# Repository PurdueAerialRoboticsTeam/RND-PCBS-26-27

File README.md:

2026-27 Git Repo for RND PCB designs. 25-26 reference designs available in archive

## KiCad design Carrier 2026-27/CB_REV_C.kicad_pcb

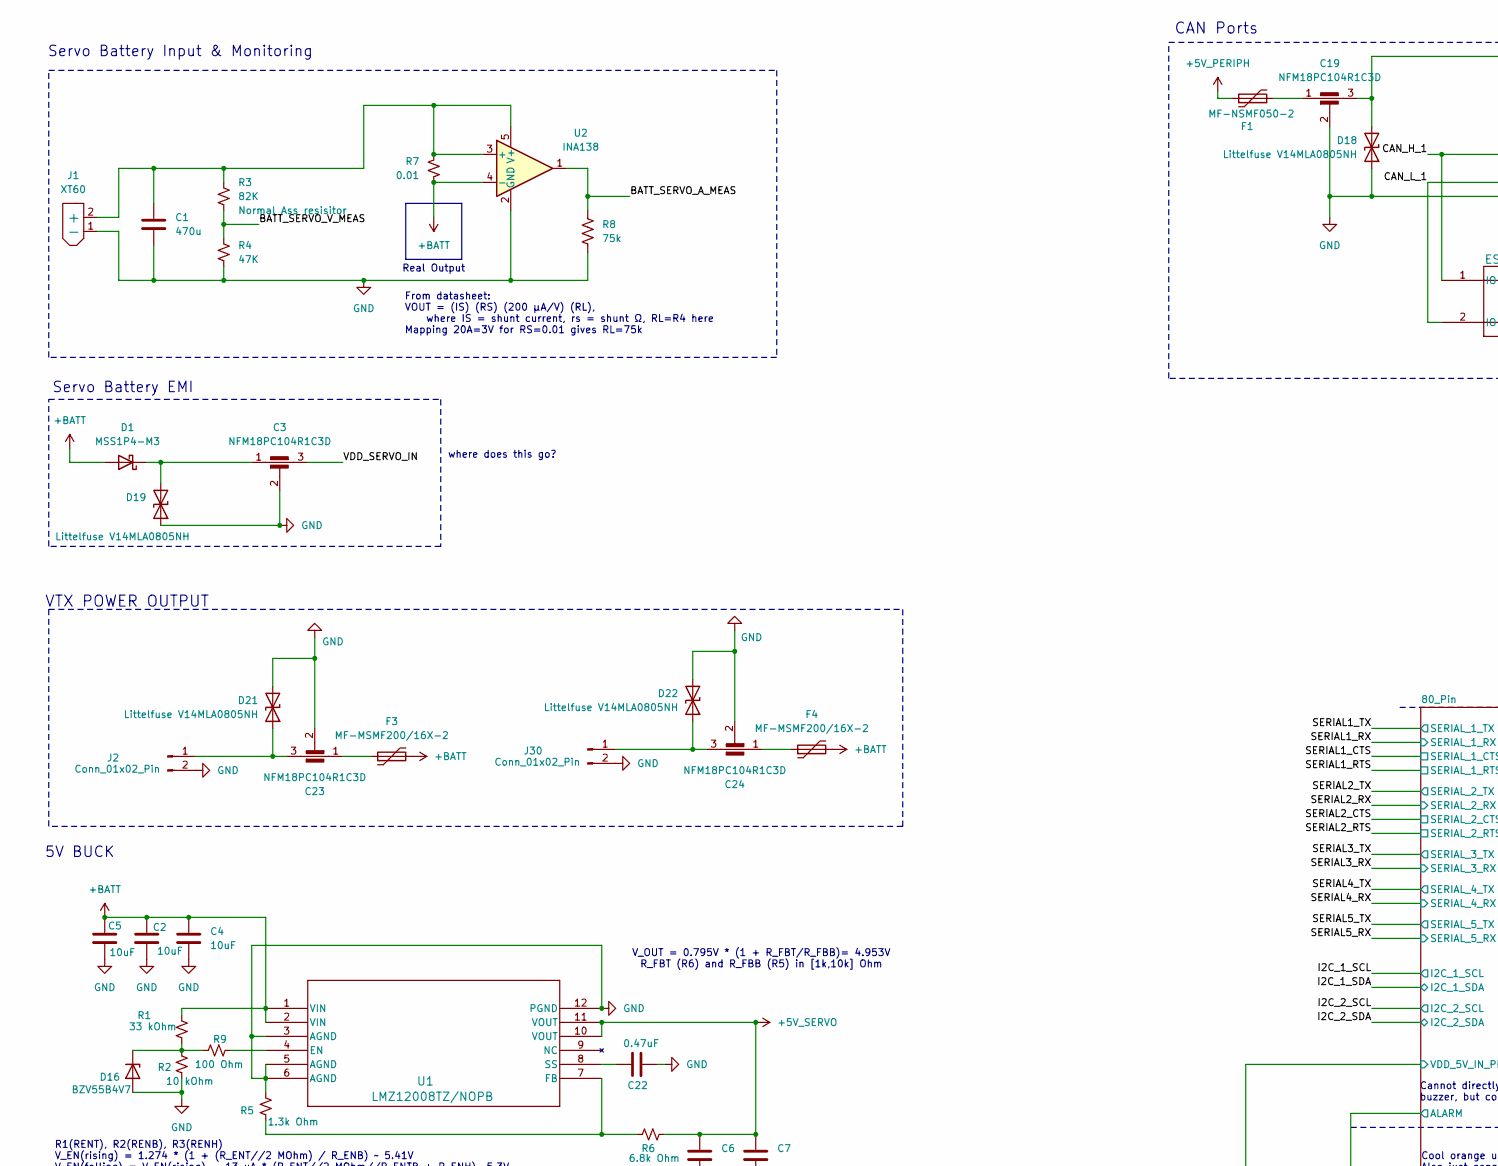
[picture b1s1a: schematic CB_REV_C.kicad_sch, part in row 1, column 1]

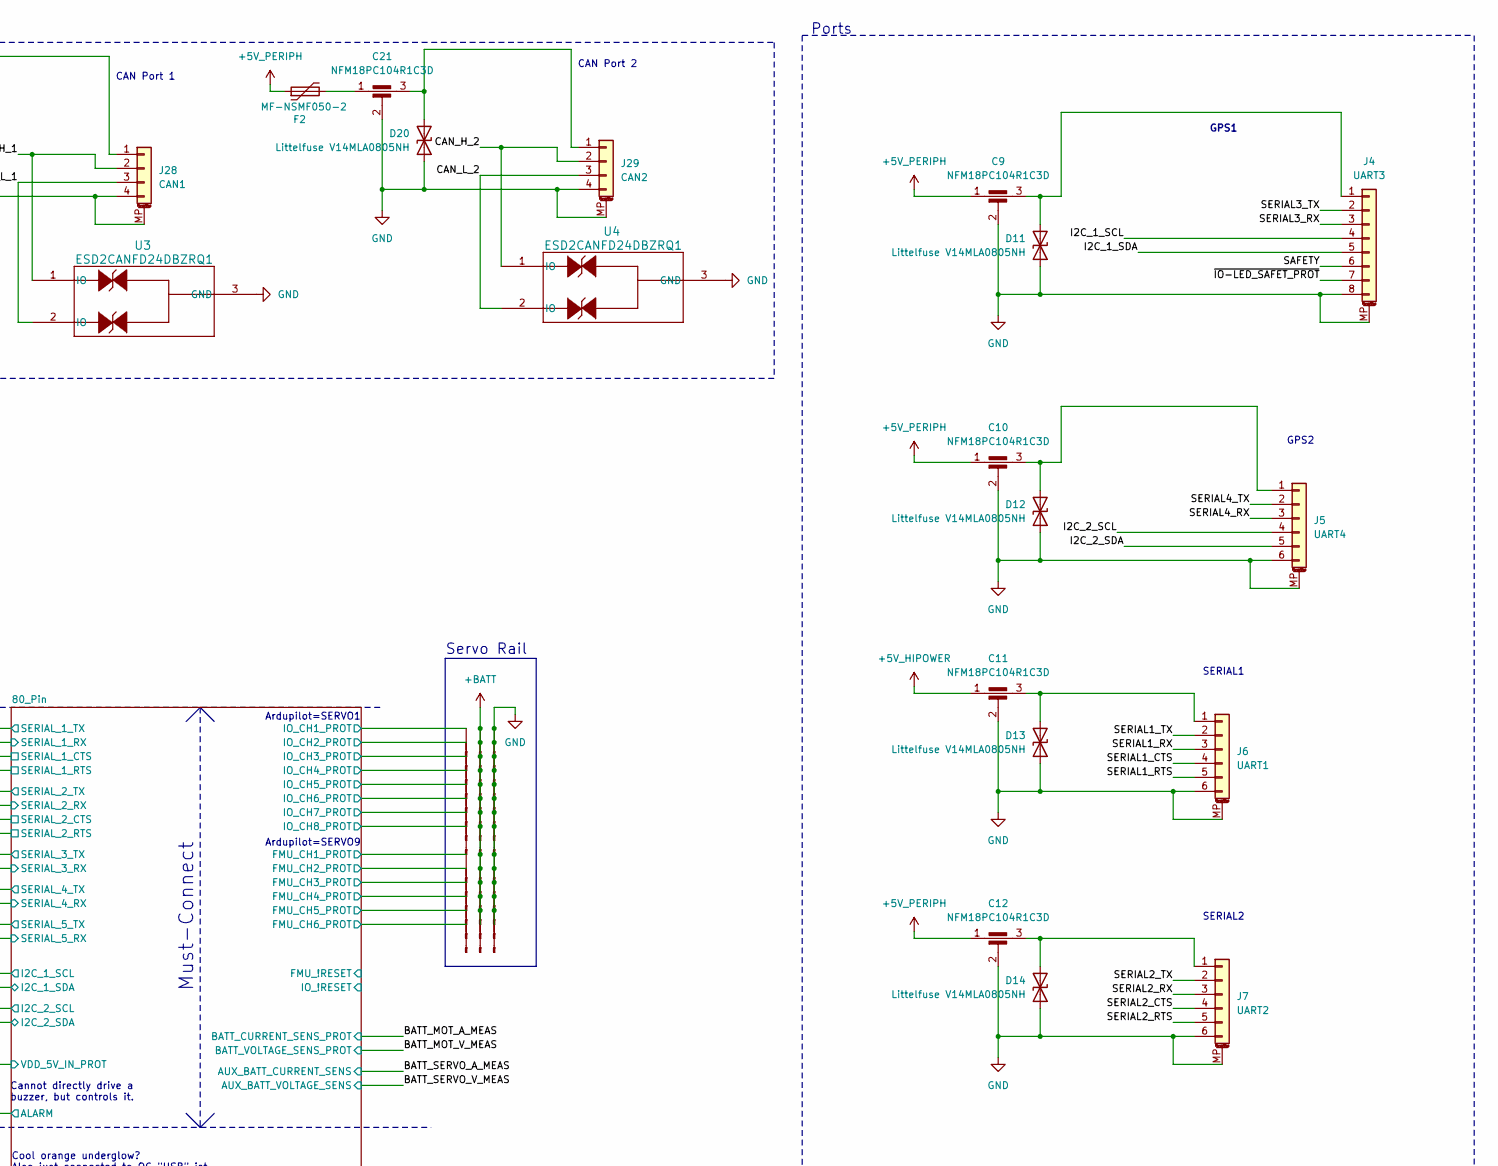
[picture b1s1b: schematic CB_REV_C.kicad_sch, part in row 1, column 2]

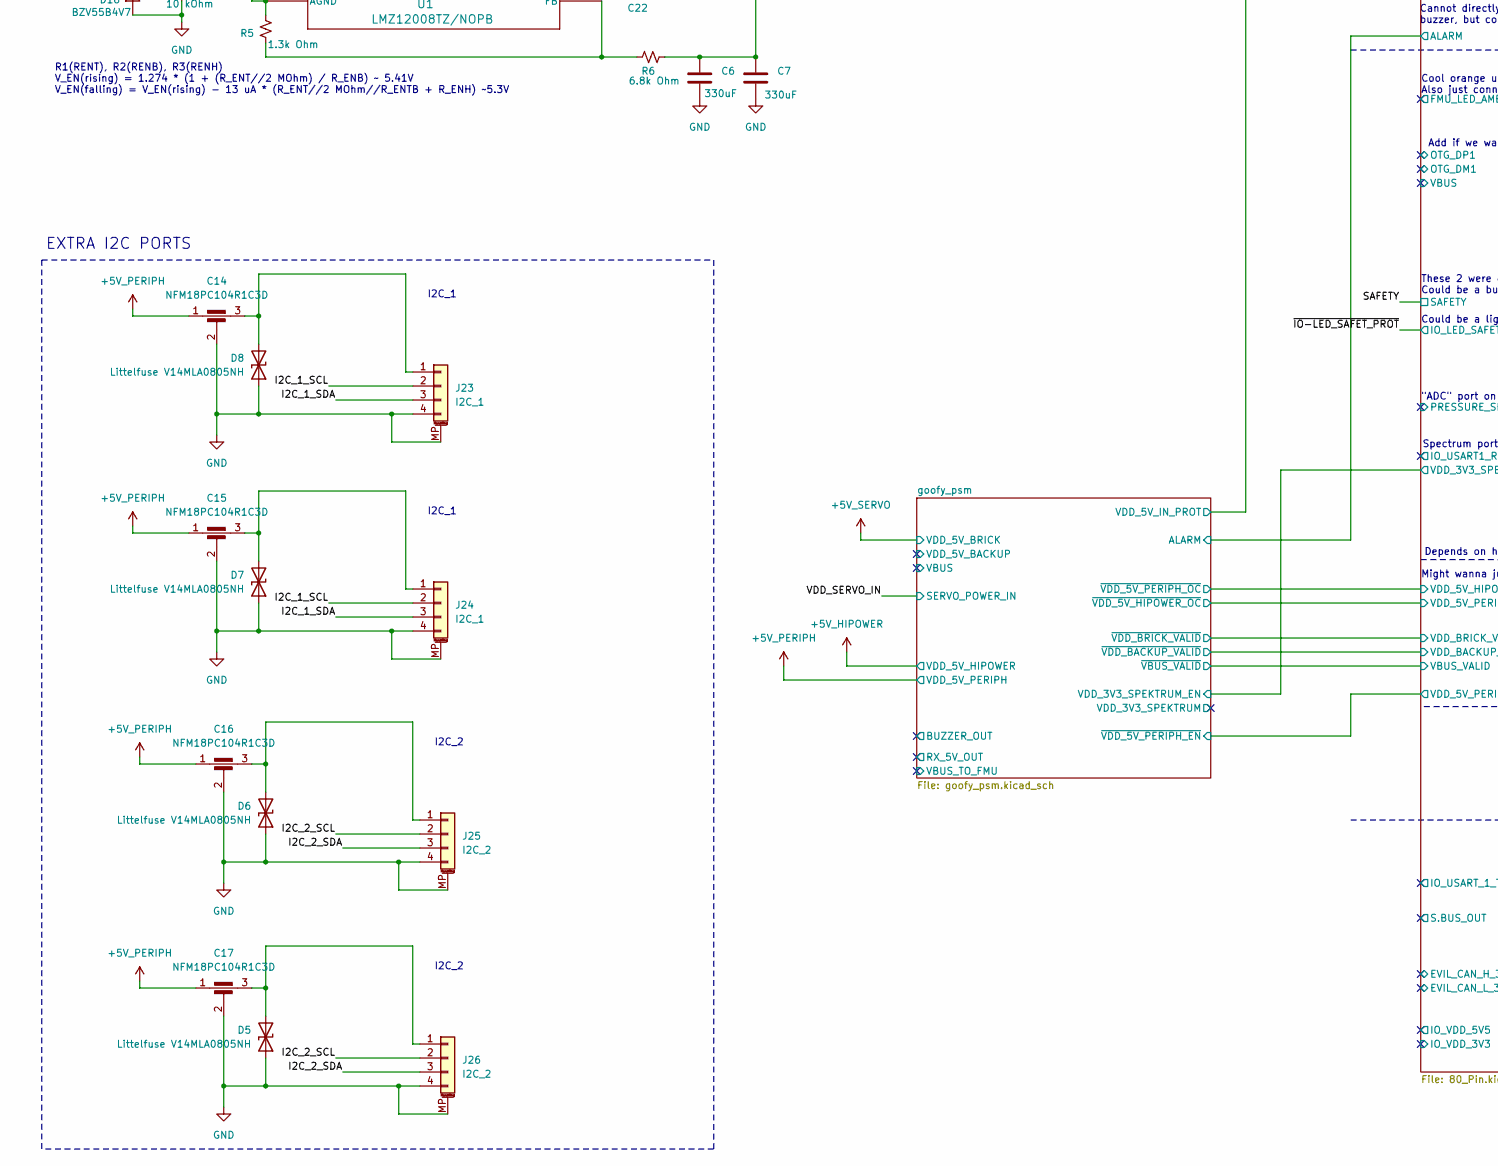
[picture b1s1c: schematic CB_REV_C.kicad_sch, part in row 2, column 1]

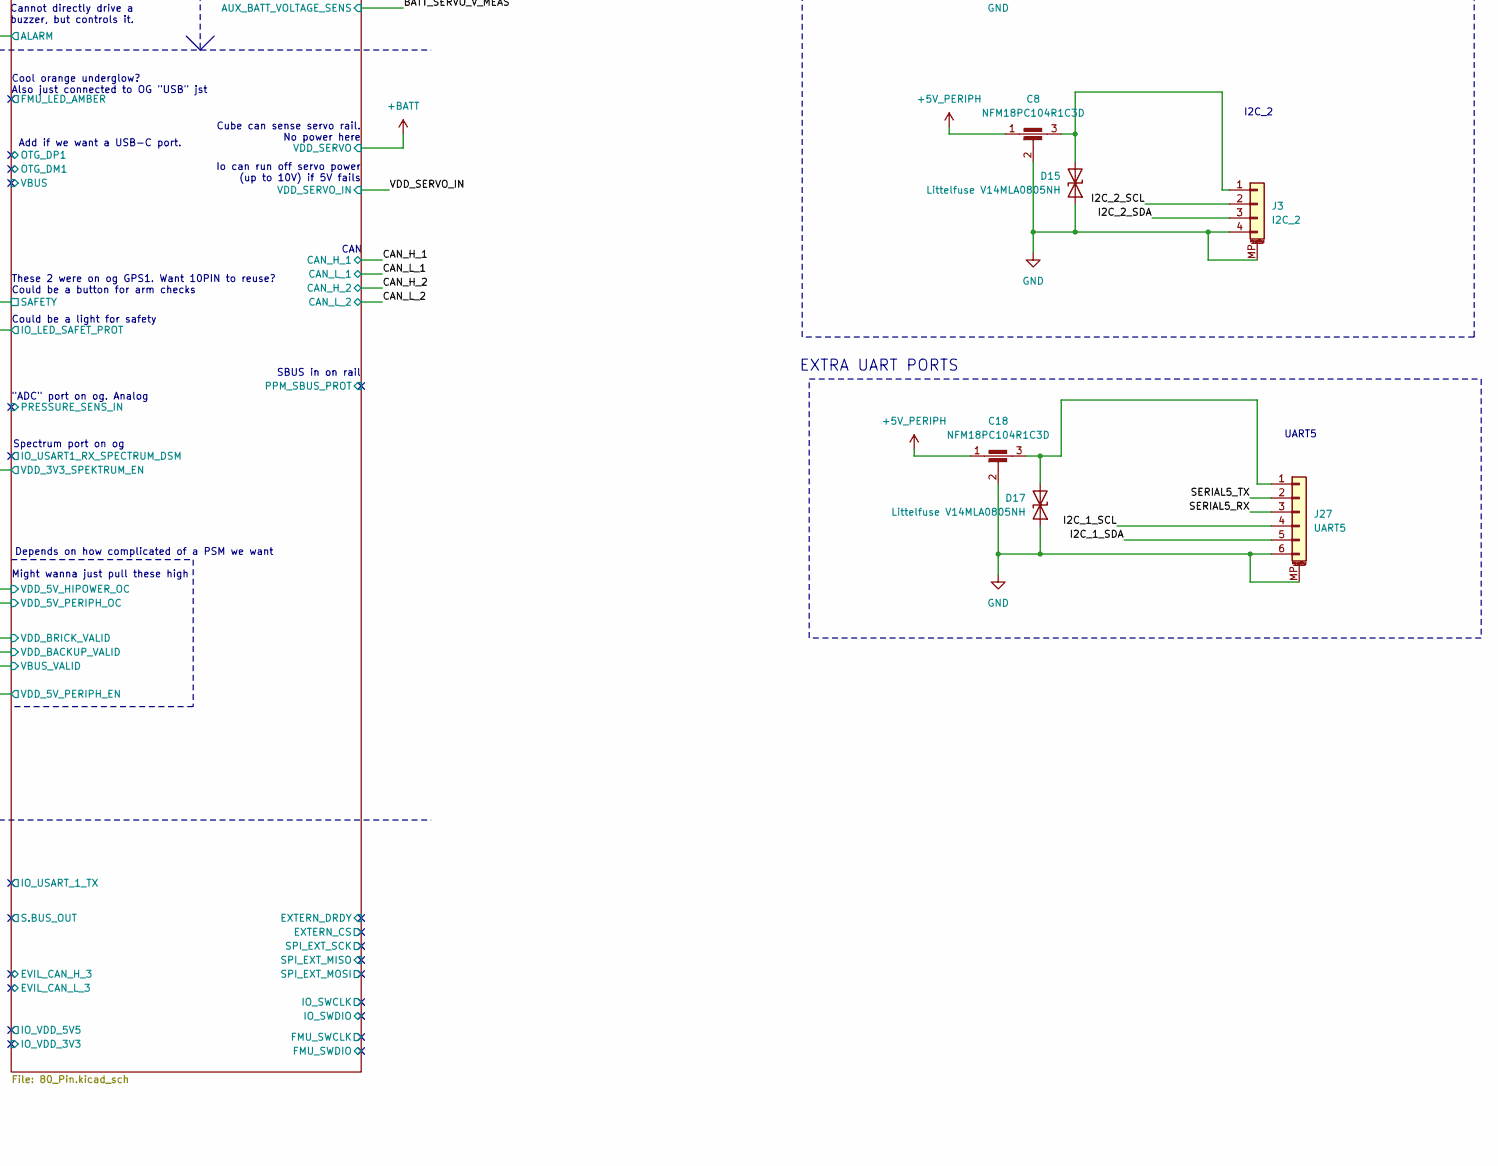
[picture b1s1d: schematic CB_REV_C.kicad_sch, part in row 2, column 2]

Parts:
C1: 470u; CP_Radial_D10.0mm_P5.00mm
C2, C4, C5: 10uF; C_1210_3225Metric_Pad1.33x2.70mm_HandSolder
C3, C8, C9, C10, C11, C12, C14, C15, C16, C17, C18, C19, C21, C23, C24: NFM18PC104R1C3D; FIL_NFM18PC104R1C3D
C6, C7: 330uF; CP_EIA-7343-31_Kemet-D_HandSolder
C22: 0.47uF; C_0805_2012Metric_Pad1.18x1.45mm_HandSolder
D1: MSS1P4-M3; MSS1P4-M3_89A
D5, D6, D7, D8, D11, D12, D13, D14, D15, D17, D18, D19, D20, D21, D22: Littelfuse V14MLA0805NH; D_0805_2012Metric_Pad1.15x1.40mm_HandSolder
D16: BZV55B4V7; D_MiniMELF
F1, F2: MF-NSMF050-2; Fuse_1206_3216Metric_Pad1.42x1.75mm_HandSolder
F3, F4: MF-MSMF200/16X-2; Fuse_1812_4532Metric_Pad1.30x3.40mm_HandSolder
J1: XT60; AMASS_XT60PW-M_1x02_P7.20mm_Horizontal
J2, J30: Conn_01x02_Pin; AMASS_XT30PW-M_1x02_P2.50mm_Horizontal
J3, J25, J26: I2C_2; JST_GH_BM04B-GHS-TBT_1x04-1MP_P1.25mm_Vertical
J4: UART3; JST_GH_BM08B-GHS-TBT_1x08-1MP_P1.25mm_Vertical
J5: UART4; JST_GH_BM06B-GHS-TBT_1x06-1MP_P1.25mm_Vertical
J6: UART1; JST_GH_BM06B-GHS-TBT_1x06-1MP_P1.25mm_Vertical
J7: UART2; JST_GH_BM06B-GHS-TBT_1x06-1MP_P1.25mm_Vertical
J8, J9, J10, J11, J12, J13, J14, J15, J16, J17, J18, J19, J20, J21: Conn_01x03_Pin; PinHeader_1x03_P2.54mm_Vertical
J23, J24: I2C_1; JST_GH_BM04B-GHS-TBT_1x04-1MP_P1.25mm_Vertical
J27: UART5; JST_GH_BM06B-GHS-TBT_1x06-1MP_P1.25mm_Vertical
J28: CAN1; JST_GH_BM04B-GHS-TBT_1x04-1MP_P1.25mm_Vertical
J29: CAN2; JST_GH_BM04B-GHS-TBT_1x04-1MP_P1.25mm_Vertical
R1: 33 kOhm; R_0805_2012Metric_Pad1.20x1.40mm_HandSolder
R2: 10 kOhm; R_0805_2012Metric_Pad1.20x1.40mm_HandSolder
R3: 82K; R_0805_2012Metric_Pad1.20x1.40mm_HandSolder; Part Number Normal Ass resisitor
R4: 47K; R_0805_2012Metric_Pad1.20x1.40mm_HandSolder
R5: 1.3k Ohm; R_0805_2012Metric_Pad1.20x1.40mm_HandSolder
R6: 6.8k Ohm; R_0805_2012Metric_Pad1.20x1.40mm_HandSolder
R7: 0.01; R_2512_6332Metric_Pad1.40x3.35mm_HandSolder
R8: 75k; R_0603_1608Metric_Pad0.98x0.95mm_HandSolder
R9: 100 Ohm; R_0805_2012Metric_Pad1.20x1.40mm_HandSolder
U1: LMZ12008TZ/NOPB; TZA11A
U2: INA138; SOT-23-5
U3, U4: ESD2CANFD24DBZRQ1; SOT_24DBZR_TEX

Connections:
+5V_SERVO: C6.1, C7.1, C8.1, C9.1, C10.1, C11.1, C12.1, C14.1, C15.1, C16.1, C17.1, C18.1, F1.1, F2.1, R6.1, U1.10 (VOUT), U1.11 (VOUT); also elsewhere on the board
+BATT: C2.1, C4.1, C5.1, D1.2 (A), F3.2, F4.2, J8.2, J9.2, J10.2, J11.2, J12.2, J13.2, J14.2, J15.2, J16.2, J17.2, J18.2, J19.2, J20.2, J21.2, R1.1, R7.2, U1.1 (VIN), U1.2 (VIN), U2.4 (-); also elsewhere on the board
/80_Pin/FMU_CH1_PROT: J16.3; also elsewhere on the board
/80_Pin/FMU_CH2_PROT: J17.3; also elsewhere on the board
/80_Pin/FMU_CH3_PROT: J18.3; also elsewhere on the board
/80_Pin/FMU_CH4_PROT: J19.3; also elsewhere on the board
/80_Pin/FMU_CH5_PROT: J20.3; also elsewhere on the board
/80_Pin/FMU_CH6_PROT: J21.3; also elsewhere on the board
/80_Pin/IO_CH1_PROT: J8.3; also elsewhere on the board
/80_Pin/IO_CH2_PROT: J9.3; also elsewhere on the board
/80_Pin/IO_CH3_PROT: J10.3; also elsewhere on the board
/80_Pin/IO_CH4_PROT: J11.3; also elsewhere on the board
/80_Pin/IO_CH5_PROT: J12.3; also elsewhere on the board
/80_Pin/IO_CH6_PROT: J13.3; also elsewhere on the board
/80_Pin/IO_CH7_PROT: J14.3; also elsewhere on the board
/80_Pin/IO_CH8_PROT: J15.3; also elsewhere on the board
/BATT_SERVO_A_MEAS: R8.1, U2.1; also elsewhere on the board
/BATT_SERVO_V_MEAS: R3.2, R4.2; also elsewhere on the board
/CAN_H_1: J28.2, U3.1 (IO); also elsewhere on the board
/CAN_H_2: J29.2, U4.1 (IO); also elsewhere on the board
/CAN_L_1: J28.3, U3.2 (IO); also elsewhere on the board
/CAN_L_2: J29.3, U4.2 (IO); also elsewhere on the board
/I2C_1_SCL: J4.4, J23.2, J24.2, J27.4; also elsewhere on the board
/I2C_1_SDA: J4.5, J23.3, J24.3, J27.5; also elsewhere on the board
/I2C_2_SCL: J3.2, J5.4, J25.2, J26.2; also elsewhere on the board
/I2C_2_SDA: J3.3, J5.5, J25.3, J26.3; also elsewhere on the board
/SAFETY: J4.6; also elsewhere on the board
/SERIAL1_CTS: J6.4; also elsewhere on the board
/SERIAL1_RTS: J6.5; also elsewhere on the board
/SERIAL1_RX: J6.3; also elsewhere on the board
/SERIAL1_TX: J6.2; also elsewhere on the board
/SERIAL2_CTS: J7.4; also elsewhere on the board
/SERIAL2_RTS: J7.5; also elsewhere on the board
/SERIAL2_RX: J7.3; also elsewhere on the board
/SERIAL2_TX: J7.2; also elsewhere on the board
/SERIAL3_RX: J4.3; also elsewhere on the board
/SERIAL3_TX: J4.2; also elsewhere on the board
/SERIAL4_RX: J5.3; also elsewhere on the board
/SERIAL4_TX: J5.2; also elsewhere on the board
/SERIAL5_RX: J27.3; also elsewhere on the board
/SERIAL5_TX: J27.2; also elsewhere on the board
/VDD_SERVO_IN: C3.3; also elsewhere on the board
/~IO-LED_SAFET_PROT: J4.7; also elsewhere on the board
GND: C1.2, C2.2, C3.2, C4.2, C5.2, C6.2, C7.2, C8.2, C9.2, C10.2, C11.2, C12.2, C14.2, C15.2, C16.2, C17.2, C18.2, C19.2, C21.2, C22.1, C23.2, C24.2, D5.1 (A1), D6.1 (A1), D7.1 (A1), D8.1 (A1), D11.1 (A1), D12.1 (A1), D13.1 (A1), D14.1 (A1), D15.1 (A1), D16.2 (A), D17.1 (A1), D18.1 (A1), D19.1 (A1), D20.1 (A1), D21.2 (A2), D22.2 (A2), J1.1 (-), J2.2, J3.4, J3.MP (MountPin), J4.8, J4.MP (MountPin), J5.6, J5.MP (MountPin), J6.6, J6.MP (MountPin), J7.6, J7.MP (MountPin), J8.1, J9.1, J10.1, J11.1, J12.1, J13.1, J14.1, J15.1, J16.1, J17.1, J18.1, J19.1, J20.1, J21.1, J23.4, J23.MP (MountPin), J24.4, J24.MP (MountPin), J25.4, J25.MP (MountPin), J26.4, J26.MP (MountPin), J27.6, J27.MP (MountPin), J28.4, J28.MP (MountPin), J29.4, J29.MP (MountPin), J30.2, R2.1, R4.1, R5.2, R8.2, U1.3 (AGND), U1.5 (AGND), U1.6 (AGND), U1.12 (PGND), U2.2 (GND), U3.3 (GND), U4.3 (GND); also elsewhere on the board
unnamed: C19.1, F1.2
unnamed: C21.1, F2.2
unnamed: C23.1, F3.1
unnamed: C24.1, F4.1
unnamed: C3.1, D1.1 (K), D19.2 (A2)
unnamed: C17.3, D5.2 (A2), J26.1
unnamed: C16.3, D6.2 (A2), J25.1
unnamed: C15.3, D7.2 (A2), J24.1
unnamed: C14.3, D8.2 (A2), J23.1
unnamed: C9.3, D11.2 (A2), J4.1
unnamed: C10.3, D12.2 (A2), J5.1
unnamed: C11.3, D13.2 (A2), J6.1
unnamed: C12.3, D14.2 (A2), J7.1
unnamed: C8.3, D15.2 (A2), J3.1
unnamed: D16.1 (K), R1.2, R2.2, R9.2
unnamed: C18.3, D17.2 (A2), J27.1
unnamed: C19.3, D18.2 (A2), J28.1
unnamed: C21.3, D20.2 (A2), J29.1
unnamed: C23.3, D21.1 (A1), J2.1
unnamed: C24.3, D22.1 (A1), J30.1
unnamed: C1.1, J1.2 (+), R3.1, R7.1, U2.3 (+), U2.5 (V+)
unnamed: R9.1, U1.4 (EN)
unnamed: R5.1, R6.2, U1.7 (FB)
unnamed: C22.2, U1.8 (SS)

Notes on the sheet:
Servo Rail
I2C_2
where does this go?
5V BUCK
Cannot directly drive a buzzer, but controls it.
Add if we want a USB-C port.
GPS1
SBUS in on rail
EXTRA I2C PORTS
"ADC" port on og. Analog
Spectrum port on og
I2C_1
Real Output
VTX POWER OUTPUT
EXTRA UART PORTS
Could be a light for safety
UART5
Ports
Might wanna just pull these high
Cool orange underglow? Also just connected to OG "USB" jst
Could be a button for arm checks
R1(RENT), R2(RENB), R3(RENH) V_EN(rising) = 1.274 * (1 + (R_ENT//2 MOhm) / R_ENB) ~ 5.41V V_EN(falling) = V_EN(rising) - 13 uA * (R_ENT//2 MOhm//R_ENTB + R_ENH) ~5.3V
CAN Port 1
Servo Battery EMI
Depends on how complicated of a PSM we want
From datasheet: VOUT = (IS) (RS) (200 μA/V) (RL), where IS = shunt current, rs = shunt Ω, RL=R4 here Mapping 20A=3V for RS=0.01 gives RL=75k
SERIAL2
These 2 were on og GPS1. Want 10PIN to reuse?
Cube can sense servo rail. No power here
Ardupilot=SERVO1
GPS2
Io can run off servo power (up to 10V) if 5V fails
CAN Port 2
CAN
CAN Ports
Ardupilot=SERVO9
Servo Battery Input & Monitoring
Must-Connect
V_OUT = 0.795V * (1 + R_FBT/R_FBB)= 4.953V R_FBT (R6) and R_FBB (R5) in [1k,10k] Ohm
SERIAL1

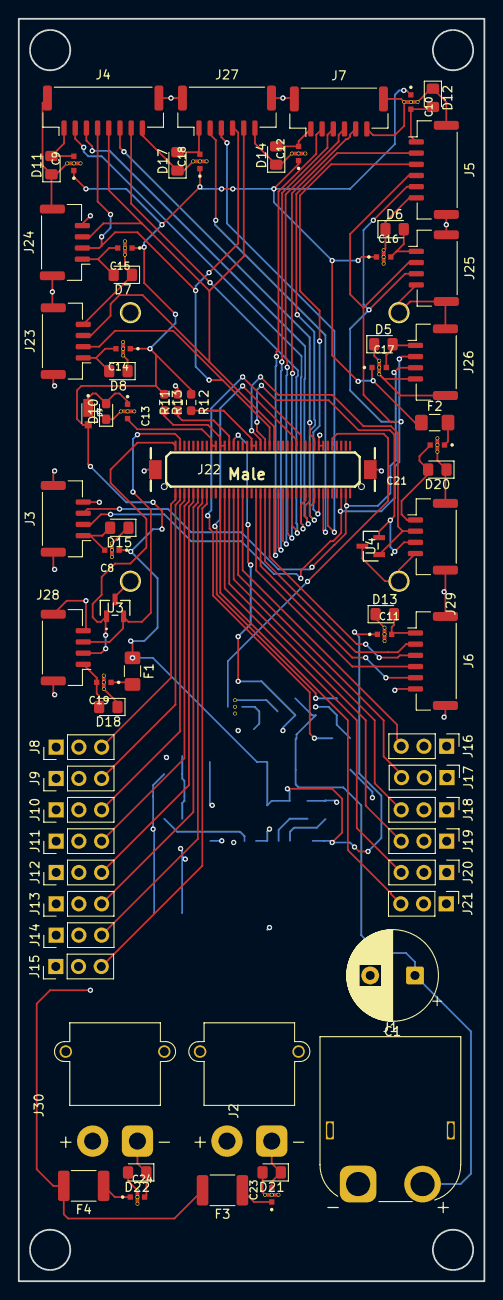
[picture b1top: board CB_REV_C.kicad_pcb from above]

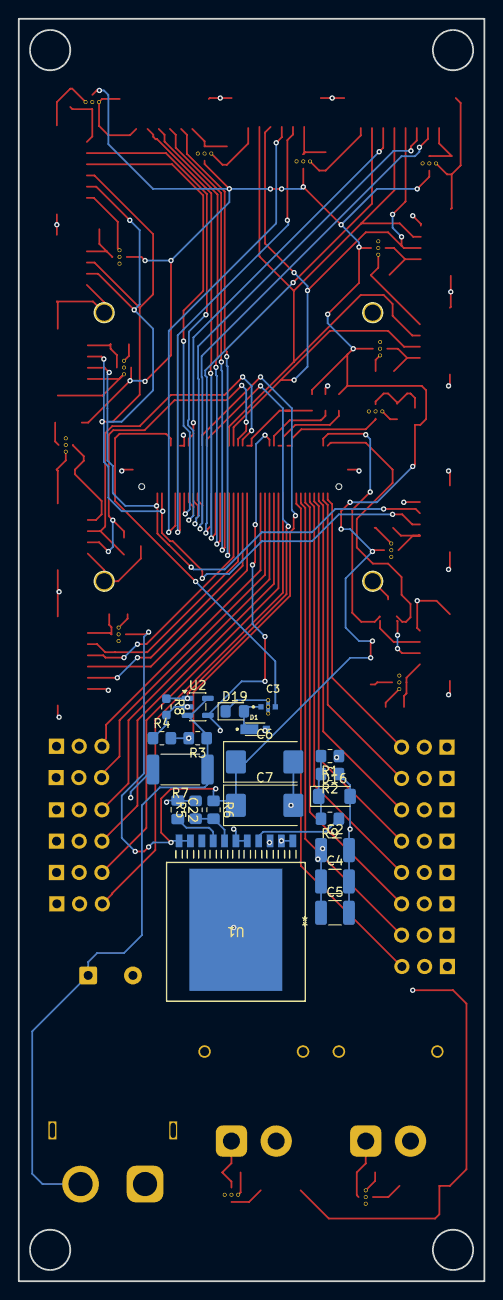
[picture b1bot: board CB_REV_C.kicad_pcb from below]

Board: 4 copper layers, 52.0 x 141.0 mm, 92 parts (21 on the bottom side), 73 nets.

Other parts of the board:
C13: NFM18PC104R1C3D; FIL_NFM18PC104R1C3D
D9: MSS1P4-M3; MSS1P4-M3_89A
D10: PESD0402-140; D_0603_1608Metric_Pad1.05x0.95mm_HandSolder
J22: Cube80Pin; CON-DF17-80M
R11, R12, R13: 100k; R_0603_1608Metric_Pad0.98x0.95mm_HandSolder

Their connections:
+5V_SERVO: D9.2 (A), R12.1, R13.1; also elsewhere on the board
+BATT: J22.53; also elsewhere on the board
/80_Pin/FMU_CH1_PROT: J22.50; also elsewhere on the board
/80_Pin/FMU_CH2_PROT: J22.52; also elsewhere on the board
/80_Pin/FMU_CH3_PROT: J22.54; also elsewhere on the board
/80_Pin/FMU_CH4_PROT: J22.56; also elsewhere on the board
/80_Pin/FMU_CH5_PROT: J22.58; also elsewhere on the board
/80_Pin/FMU_CH6_PROT: J22.60; also elsewhere on the board
/80_Pin/IO_CH1_PROT: J22.80; also elsewhere on the board
/80_Pin/IO_CH2_PROT: J22.78; also elsewhere on the board
/80_Pin/IO_CH3_PROT: J22.76; also elsewhere on the board
/80_Pin/IO_CH4_PROT: J22.74; also elsewhere on the board
/80_Pin/IO_CH5_PROT: J22.72; also elsewhere on the board
/80_Pin/IO_CH6_PROT: J22.70; also elsewhere on the board
/80_Pin/IO_CH7_PROT: J22.68; also elsewhere on the board
/80_Pin/IO_CH8_PROT: J22.66; also elsewhere on the board
/80_Pin/VBUS_VALID: J22.57, J22.59, R13.2
/80_Pin/VDD_5V_HIPOWER_OC: J22.43, J22.45, R12.2
/80_Pin/VDD_5V_IN_PROT: C13.3, J22.61, J22.63
/80_Pin/VDD_BRICK_VALID: J22.55, R11.1
/BATT_SERVO_A_MEAS: J22.25; also elsewhere on the board
/BATT_SERVO_V_MEAS: J22.23; also elsewhere on the board
/CAN_H_1: J22.79; also elsewhere on the board
/CAN_H_2: J22.41; also elsewhere on the board
/CAN_L_1: J22.77; also elsewhere on the board
/CAN_L_2: J22.39; also elsewhere on the board
/I2C_1_SCL: J22.37; also elsewhere on the board
/I2C_1_SDA: J22.35; also elsewhere on the board
/I2C_2_SCL: J22.6; also elsewhere on the board
/I2C_2_SDA: J22.4; also elsewhere on the board
/SAFETY: J22.17; also elsewhere on the board
/SERIAL1_CTS: J22.44; also elsewhere on the board
/SERIAL1_RTS: J22.42; also elsewhere on the board
/SERIAL1_RX: J22.38; also elsewhere on the board
/SERIAL1_TX: J22.40; also elsewhere on the board
/SERIAL2_CTS: J22.32; also elsewhere on the board
/SERIAL2_RTS: J22.30; also elsewhere on the board
/SERIAL2_RX: J22.34; also elsewhere on the board
/SERIAL2_TX: J22.36; also elsewhere on the board
/SERIAL3_RX: J22.20; also elsewhere on the board
/SERIAL3_TX: J22.22; also elsewhere on the board
/SERIAL4_RX: J22.16; also elsewhere on the board
/SERIAL4_TX: J22.18; also elsewhere on the board
/SERIAL5_RX: J22.12; also elsewhere on the board
/SERIAL5_TX: J22.14; also elsewhere on the board
/VDD_SERVO_IN: J22.9; also elsewhere on the board
/~IO-LED_SAFET_PROT: J22.28; also elsewhere on the board
GND: C13.2, D10.1 (A1), J22.13, J22.15, J22.GND, R11.2; also elsewhere on the board
unnamed: C13.1, D9.1 (K), D10.2 (A2)
